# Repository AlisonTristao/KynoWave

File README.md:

# KynoWave

O **KynoWave** é um projeto de hardware focado na monitorização de ruído acústico em ambientes. Desenvolvido em torno do microcontrolador ESP32-S3. 

O projeto foi desenvolvido para participar do desafio da Maratona de Inovação 2026/1, realizada no evento Arena Ação Jr.

Todo o desenvolvimento de hardware e software foi realizado em menos de um mês, dentro do prazo proposto pelo desafio, e o projeto conquistou o 2º lugar na competição.

## Características Principais

* **Microcontrolador:** ESP32-S3.
* **Entradas de Áudio:** Capacidade para a ligação de até 2 microfones, com ganho ajustável entre 2x e 22x.
* **Filtro Anti-aliasing:** Filtro anti-aliasing configurado para 100kHz.
* **Ecrã LCD:** Conexão otimizada via cabo flat (FPC) para interface SPI com ecrã LCD.
* **Sensores Ambientais:** Integração com sensores de pressão, temperatura e humidade.
* **Armazenamento Local:** Interface para cartão de memória usando conexão SPI.
* **Expansibilidade:** Disponibilização de 15 GPIOs genéricos através de um conector lateral. Estes pinos permitem a adição de sensores extra e suportam integração com módulos de câmara e sensores i2c.

Abaixo, a fotografia detalhada da PCB:

---

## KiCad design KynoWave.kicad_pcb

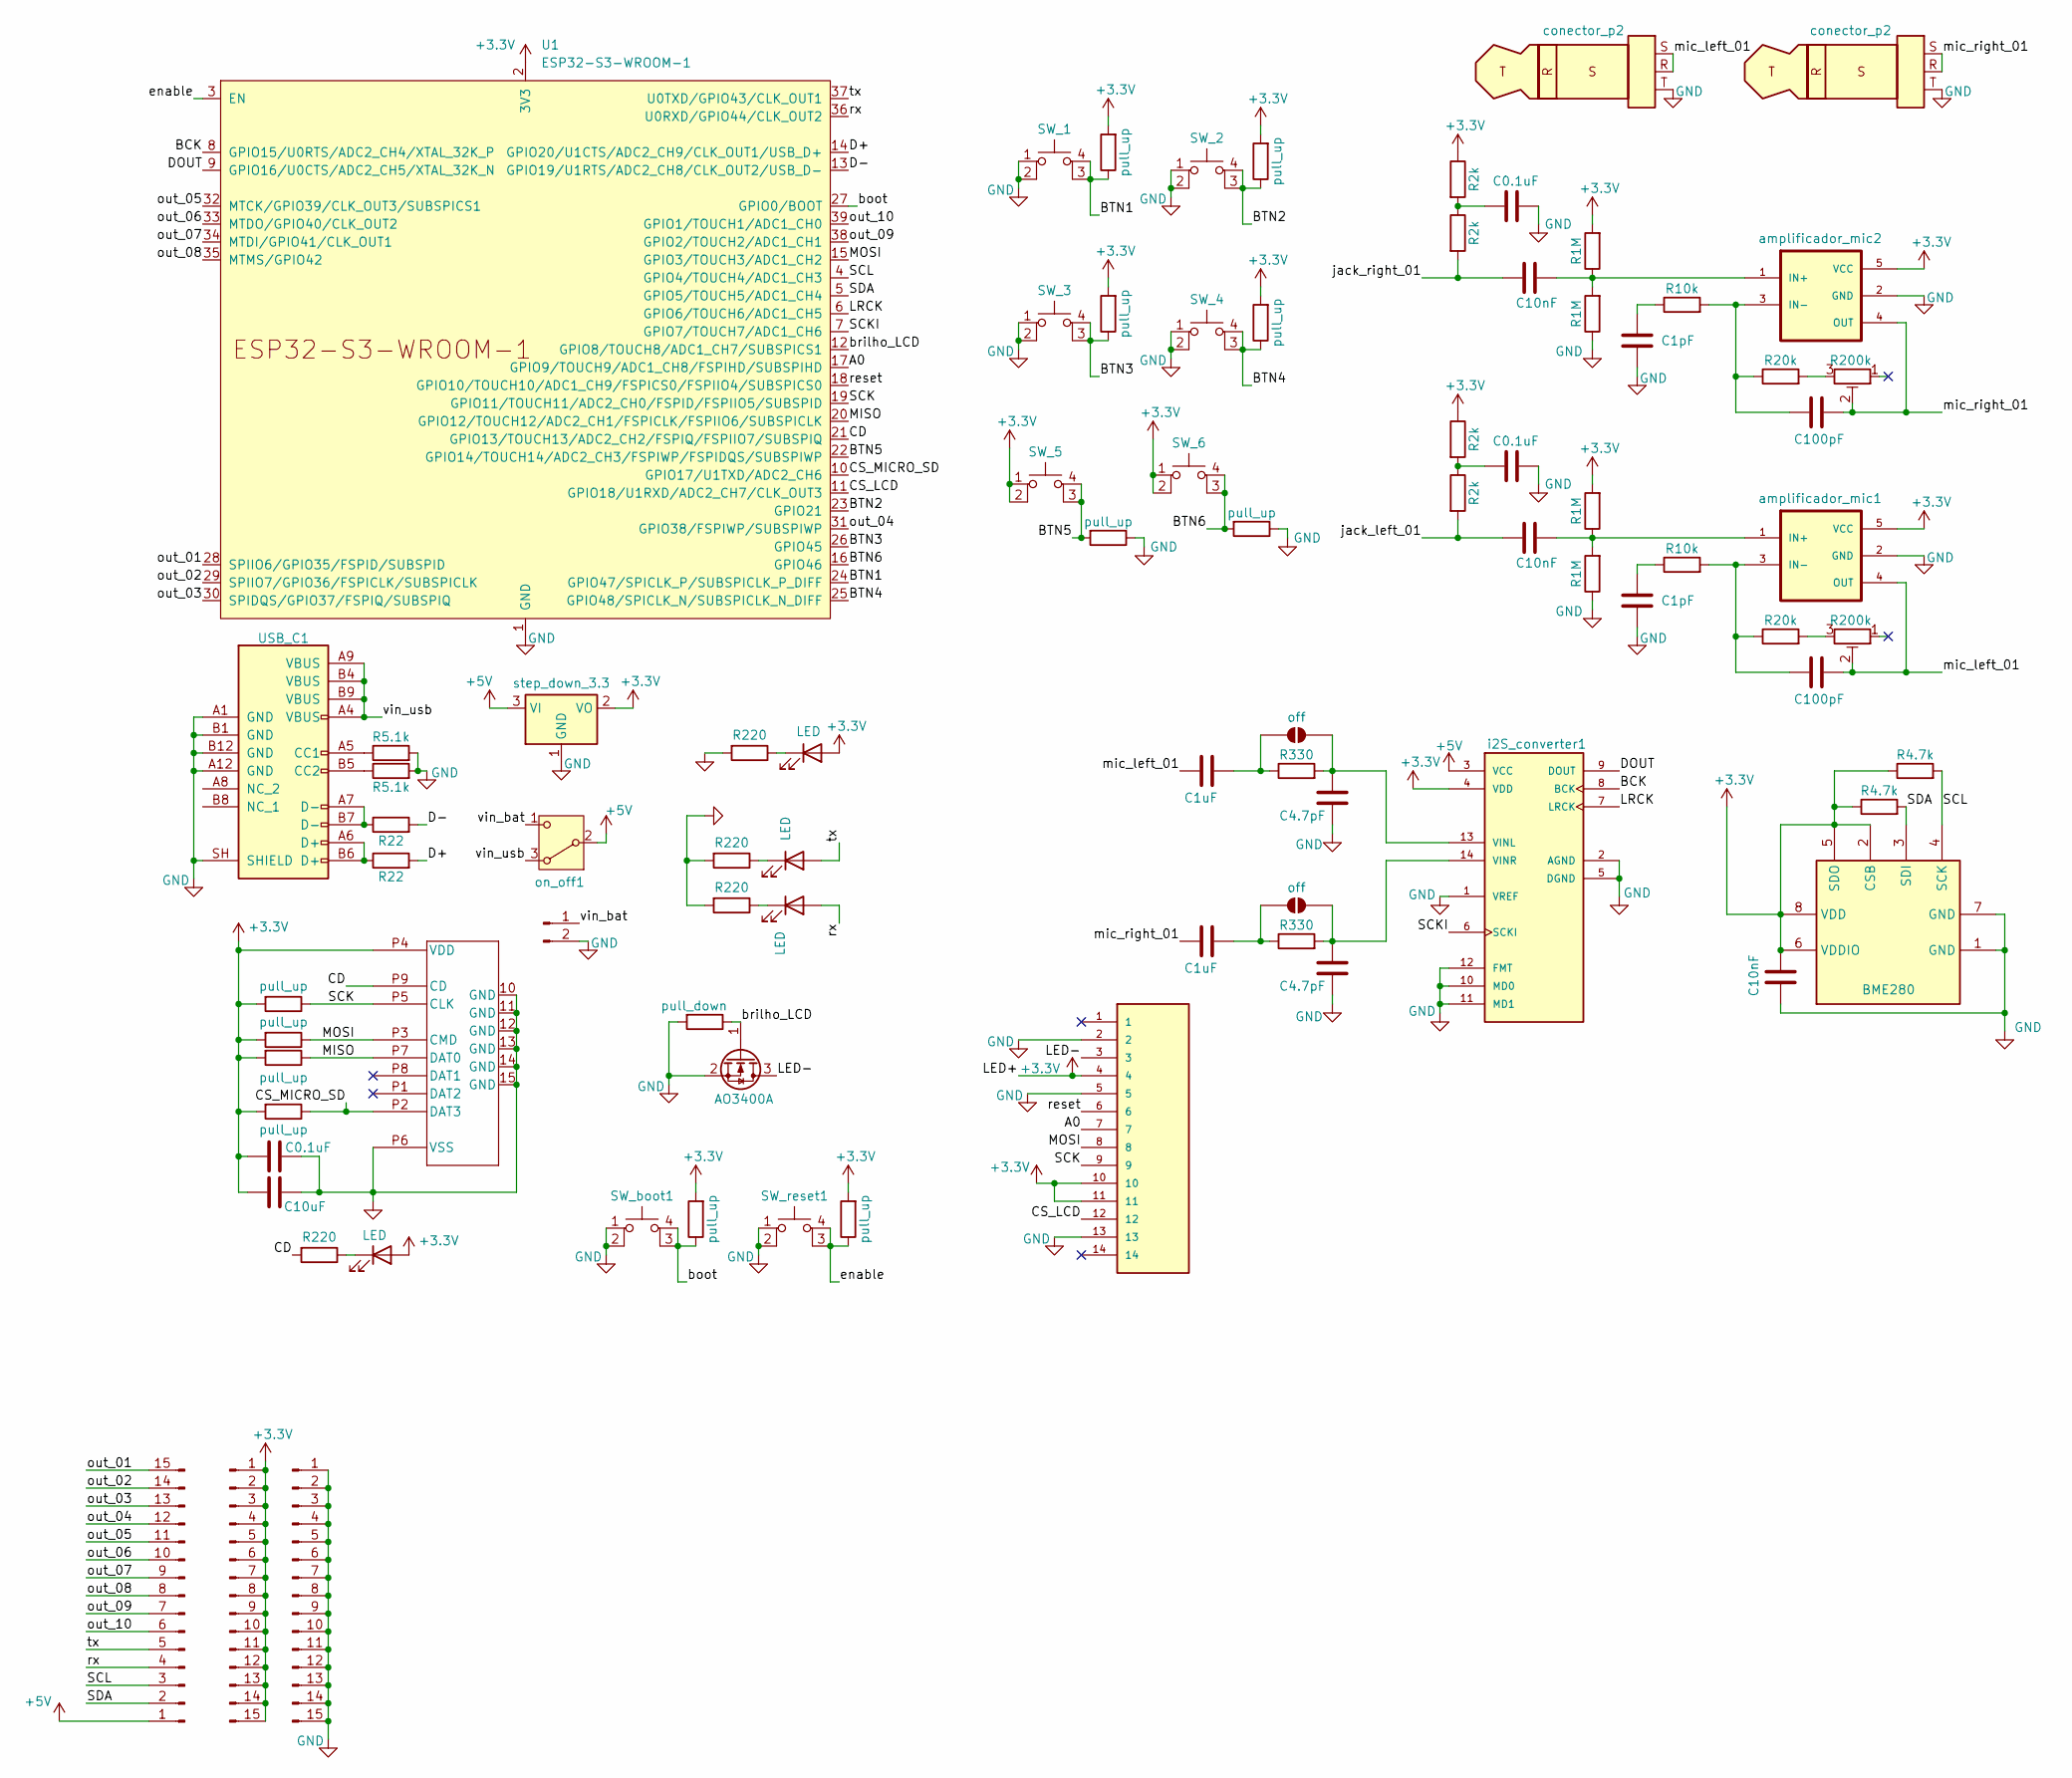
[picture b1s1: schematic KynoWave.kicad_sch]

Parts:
AudioPlug1, AudioPlug2: conector_p2; Jack_3.5mm_CUI_SJ-3523-SMT_Horizontal
C1, C8: C100pF; C_0805_2012Metric
C2, C7: C1pF; C_0805_2012Metric
C3, C6, C15: C10nF; C_0805_2012Metric
C4, C5, C9: C0.1uF; C_0805_2012Metric
C10: C10uF; C_0805_2012Metric
C11, C13: C1uF; C_0805_2012Metric
C12, C14: C4.7pF; C_0805_2012Metric
D4, D5, D6: LED; LED_0805_2012Metric
D7: LED; LED_D1.8mm_W1.8mm_H2.4mm_Horizontal_O1.27mm_Z1.6mm
J1: FFC2B35-14-G_REVA2; GCT_FFC2B35-14-G_REVA2; PARTREV A2
J2, J3, J4: Conn_01x15_Pin; PinHeader_1x15_P2.54mm_Vertical
J5: Conn_01x02_Pin; Molex_KK-254_AE-6410-02A_1x02_P2.54mm_Vertical
J6: MEM2075-00-140-01-A; MEM2075-00-140-01-A_GCT
JP1, JP2: off; SolderJumper-2_P1.3mm_Open_TrianglePad1.0x1.5mm
Q1: AO3400A; SOT-23
R1, R2: R5.1k; R_0805_2012Metric
R3, R4: R22; R_0805_2012Metric
R5, R6, R26, R27, R28, R29, R36, R37, R38, R39, R40, R41: pull_up; R_0805_2012Metric
R11, R25: R10k; R_0805_2012Metric
R12, R17, R24: R220; R_0805_2012Metric_Pad1.20x1.40mm_HandSolder
R13, R31: R20k; R_0805_2012Metric
R14, R15, R21, R22: R1M; R_0805_2012Metric
R16, R18, R19, R20: R2k; R_0805_2012Metric
R23: pull_down; R_0805_2012Metric
R30: R220; R_0805_2012Metric
R32, R33: R330; R_0805_2012Metric
R34, R35: R4.7k; R_0805_2012Metric
RV1, RV2: R200k; Potentiometer_Bourns_3314G_Vertical
SW_1, SW_2, SW_3, SW_4, SW_5, SW_6: SW_6mm_SMD; SW_TS08-66-43-BK-160-SMT-67-TR
SW_boot1: SW_6mm_SMD; SW_TS08-66-43-BK-160-SMT-67-TR
SW_reset1: SW_6mm_SMD; SW_TS08-66-43-BK-160-SMT-67-TR
U1: ESP32-S3-WROOM-1; ESP32-S3-WROOM-1U
U2: BME280; Bosch_LGA-8_2.5x2.5mm_P0.65mm_ClockwisePinNumbering
USB_C1: USB_C_Receptacle_USB2.0_14P; USB_C_Receptacle_XKB_U262-16XN-4BVC11
amplificador_mic1, amplificador_mic2: MAX4466EXK; SOT65P210X110-5N
i2S_converter1: PCM1808PWR; SOP65P640X120-14N; PARTREV B
on_off1: SW_Nidec_CAS-120A1; SW_SPDT_CK_JS102011SAQN
step_down_3.3: AMS1117-3.3; SOT-223-3_TabPin2

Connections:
+3.3V: C9.1, C10.1, C15.2, D6.2 (A), D7.2 (A), J1.4, J1.10, J1.11, J3.1, J3.2, J3.3, J3.4, J3.5, J3.6, J3.7, J3.8, J3.9, J3.10, J3.11, J3.12, J3.13, J3.14, J3.15, J6.P4 (VDD), R5.2, R6.2, R15.2, R18.1, R19.1, R21.2, R26.2, R27.2, R28.2, R29.2, R34.1, R35.1, R36.2, R37.2, R38.2, R39.2, SW_5.1, SW_5.2, SW_6.1, SW_6.2, U1.2 (3V3), U2.2 (CSB), U2.5 (SDO), U2.6 (VDDIO), U2.8 (VDD), amplificador_mic1.5 (VCC), amplificador_mic2.5 (VCC), i2S_converter1.4 (VDD), step_down_3.3.2 (VO)
+5V: J2.1, i2S_converter1.3 (VCC), on_off1.2 (B), step_down_3.3.3 (VI)
/A0: J1.7, U1.17 (GPIO9/TOUCH9/ADC1_CH8/FSPIHD/SUBSPIHD)
/BCK: U1.8 (GPIO15/U0RTS/ADC2_CH4/XTAL_32K_P), i2S_converter1.8 (BCK)
/BTN1: R36.1, SW_1.3 (K), SW_1.4 (A), U1.24 (GPIO47/SPICLK_P/SUBSPICLK_P_DIFF)
/BTN2: R37.1, SW_2.3 (K), SW_2.4 (A), U1.23 (GPIO21)
/BTN3: R38.1, SW_3.3 (K), SW_3.4 (A), U1.26 (GPIO45)
/BTN4: R39.1, SW_4.3 (K), SW_4.4 (A), U1.25 (GPIO48/SPICLK_N/SUBSPICLK_N_DIFF)
/BTN5: R40.2, SW_5.3 (K), SW_5.4 (A), U1.22 (GPIO14/TOUCH14/ADC2_CH3/FSPIWP/FSPIDQS/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)
/BTN6: R41.2, SW_6.3 (K), SW_6.4 (A), U1.16 (GPIO46)
/CD: J6.P9 (CD), R30.2, U1.21 (GPIO13/TOUCH13/ADC2_CH2/FSPIQ/FSPIIO7/S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)
/CS_LCD: J1.12, U1.11 (GPIO18/U1RXD/ADC2_CH7/CLK_OUT3)
/CS_MICRO_SD: J6.P2 (DAT3), R28.1, U1.10 (GPIO17/U1TXD/ADC2_CH6)
/D+: R3.2, U1.14 (GPIO20/U1CTS/ADC2_CH9/CLK_OUT1/USB_D+)
/D-: R4.2, U1.13 (GPIO19/U1RTS/ADC2_CH8/CLK_OUT2/USB_D-)
/DOUT: U1.9 (GPIO16/U0CTS/ADC2_CH5/XTAL_32K_N), i2S_converter1.9 (DOUT)
/LED-: J1.3, Q1.3 (D)
/LRCK: U1.6 (GPIO6/TOUCH6/ADC1_CH5), i2S_converter1.7 (LRCK)
/MISO: J6.P7 (DAT0), R26.1, U1.20 (GPIO12/TOUCH12/ADC2_CH1/FSPICLK/FSPIIO6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)
/MOSI: J1.8, J6.P3 (CMD), R27.1, U1.15 (GPIO3/TOUCH3/ADC1_CH2)
/SCK: J1.9, J6.P5 (CLK), R29.1, U1.19 (GPIO11/TOUCH11/ADC2_CH0/FSPID/FSPIIO5/S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)
/SCKI: U1.7 (GPIO7/TOUCH7/ADC1_CH6), i2S_converter1.6 (SCKI)
/SCL: J2.3, R35.2, U1.4 (GPIO4/TOUCH4/ADC1_CH3), U2.4 (SCK)
/SDA: J2.2, R34.2, U1.5 (GPIO5/TOUCH5/ADC1_CH4), U2.3 (SDI)
/boot: R5.1, SW_boot1.3 (K), SW_boot1.4 (A), U1.27 (GPIO0/BOOT)
/brilho_LCD: Q1.1 (G), R23.1, U1.12 (GPIO8/TOUCH8/ADC1_CH7/SUBSPICS1)
/enable: R6.1, SW_reset1.3 (K), SW_reset1.4 (A), U1.3 (EN)
/jack_left_01: C3.1, R16.2
/jack_right_01: C6.1, R20.2
/mic_left_01: AudioPlug1.R, AudioPlug1.S, C1.1, C13.2, RV1.2, amplificador_mic1.4 (OUT)
/mic_right_01: AudioPlug2.R, AudioPlug2.S, C8.1, C11.2, RV2.2, amplificador_mic2.4 (OUT)
/out_01: J2.15, U1.28 (SPIIO6/GPIO35/FSPID/SUBSPID)
/out_02: J2.14, U1.29 (SPIIO7/GPIO36/FSPICLK/SUBSPICLK)
/out_03: J2.13, U1.30 (SPIDQS/GPIO37/FSPIQ/SUBSPIQ)
/out_04: J2.12, U1.31 (GPIO38/FSPIWP/SUBSPIWP)
/out_05: J2.11, U1.32 (MTCK/GPIO39/CLK_OUT3/SUBSPICS1)
/out_06: J2.10, U1.33 (MTDO/GPIO40/CLK_OUT2)
/out_07: J2.9, U1.34 (MTDI/GPIO41/CLK_OUT1)
/out_08: J2.8, U1.35 (MTMS/GPIO42)
/out_09: J2.7, U1.38 (GPIO2/TOUCH2/ADC1_CH1)
/out_10: J2.6, U1.39 (GPIO1/TOUCH1/ADC1_CH0)
/reset: J1.6, U1.18 (GPIO10/TOUCH10/ADC1_CH9/FSPICS0/FSPIIO4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)
/rx: D5.2 (A), J2.4, U1.36 (U0RXD/GPIO44/CLK_OUT2)
/tx: D4.2 (A), J2.5, U1.37 (U0TXD/GPIO43/CLK_OUT1)
/vin_bat: J5.1, on_off1.1 (C)
/vin_usb: USB_C1.A4 (VBUS), USB_C1.A9 (VBUS), USB_C1.B4 (VBUS), USB_C1.B9 (VBUS), on_off1.3 (A)
GND: AudioPlug1.T, AudioPlug2.T, C2.2, C4.1, C5.1, C7.2, C9.2, C10.2, C12.2, C14.2, C15.1, J1.2, J1.5, J1.13, J4.1, J4.2, J4.3, J4.4, J4.5, J4.6, J4.7, J4.8, J4.9, J4.10, J4.11, J4.12, J4.13, J4.14, J4.15, J5.2, J6.10 (GND), J6.11 (GND), J6.12 (GND), J6.13 (GND), J6.14 (GND), J6.15 (GND), J6.P6 (VSS), Q1.2 (S), R1.2, R2.2, R12.2, R14.1, R17.2, R22.1, R23.2, R24.2, R40.1, R41.1, SW_1.1, SW_1.2, SW_2.1, SW_2.2, SW_3.1, SW_3.2, SW_4.1, SW_4.2, SW_boot1.1, SW_boot1.2, SW_reset1.1, SW_reset1.2, U1.1 (GND), U1.40 (GND), U1.41 (GND), U2.1 (GND), U2.7 (GND), USB_C1.A1 (GND), USB_C1.A12 (GND), USB_C1.B1 (GND), USB_C1.B12 (GND), USB_C1.SH (SHIELD), amplificador_mic1.2 (GND), amplificador_mic2.2 (GND), i2S_converter1.1 (VREF), i2S_converter1.2 (AGND), i2S_converter1.5 (DGND), i2S_converter1.10 (MD0), i2S_converter1.11 (MD1), i2S_converter1.12 (FMT), step_down_3.3.1 (GND)
unnamed: C2.1, R11.1
unnamed: C4.2, R16.1, R18.2
unnamed: C5.2, R19.2, R20.1
unnamed: C7.1, R25.1
unnamed: D4.1 (K), R12.1
unnamed: D5.1 (K), R17.1
unnamed: D6.1 (K), R30.1
unnamed: D7.1 (K), R24.1
unnamed: C13.1, JP1.1 (A), R33.1
unnamed: C14.1, JP1.2 (B), R33.2, i2S_converter1.13 (VINL)
unnamed: C11.1, JP2.1 (A), R32.1
unnamed: C12.1, JP2.2 (B), R32.2, i2S_converter1.14 (VINR)
unnamed: R3.1, USB_C1.A6 (D+), USB_C1.B6 (D+)
unnamed: R4.1, USB_C1.A7 (D-), USB_C1.B7 (D-)
unnamed: R13.2, RV1.3
unnamed: R31.2, RV2.3
unnamed: R1.1, USB_C1.A5 (CC1)
unnamed: R2.1, USB_C1.B5 (CC2)
unnamed: C3.2, R14.2, R15.1, amplificador_mic1.1 (IN+)
unnamed: C1.2, R11.2, R13.1, amplificador_mic1.3 (IN-)
unnamed: C6.2, R21.1, R22.2, amplificador_mic2.1 (IN+)
unnamed: C8.2, R25.2, R31.1, amplificador_mic2.3 (IN-)

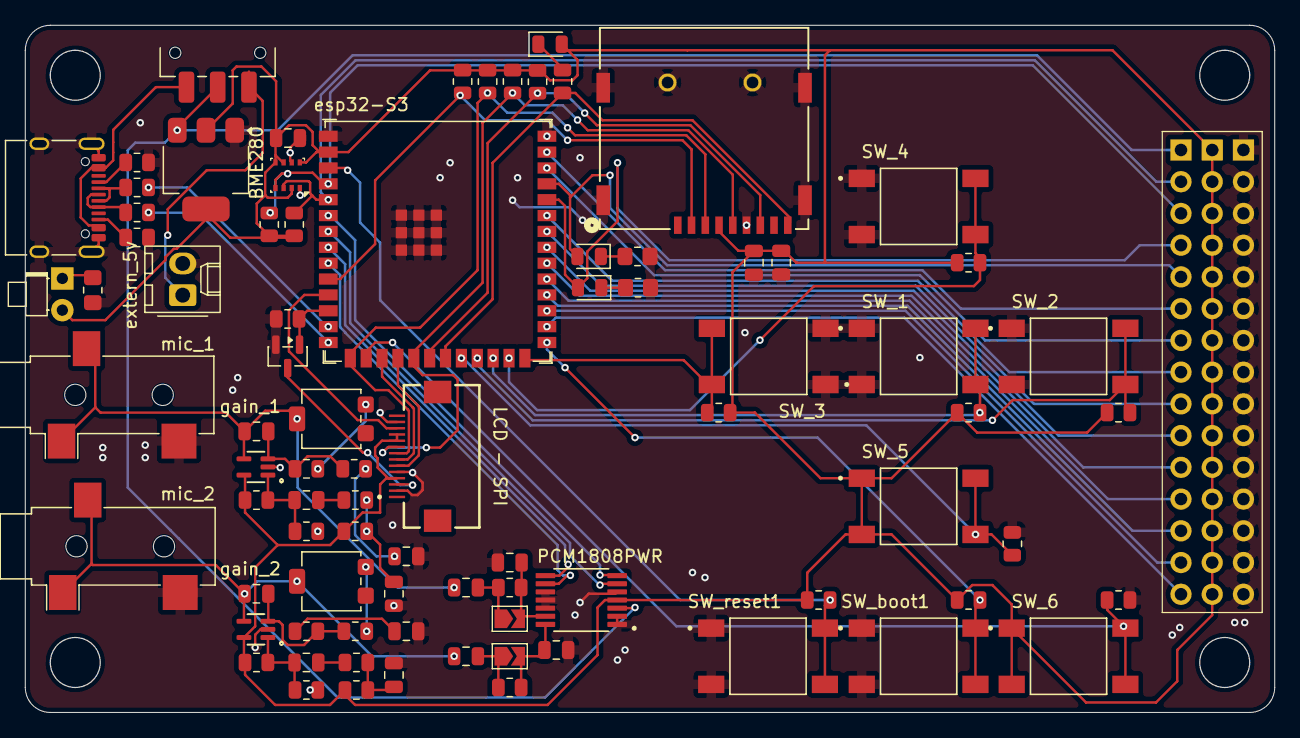
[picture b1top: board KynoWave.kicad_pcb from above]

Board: 2 copper layers, 100.0 x 55.0 mm, 85 parts (0 on the bottom side), 69 nets.

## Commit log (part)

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2026-05-03 salvando a codicao inicial antes do roteamento
2026-05-03 antes das trilhas
2026-05-03 fiz as trilhas
2026-05-06 praticamente pronto
2026-05-06 Create README.md for KynoWave
    Added project overview and key features for KynoWave.
2026-05-14 Atualizando referência da pasta de hardware
2026-05-14 apaguei o history fodase
2026-05-14 primeiro commmit
2026-05-15 logger parece funcionar
2026-05-15 lixo
2026-05-15 antes de mudar o logger pra um buffer
2026-05-15 conteudo generico no content do logger
2026-05-15 formatacao de printf
2026-05-15 comecei a organizar
2026-05-15 adiconei o shell
2026-05-16 terminal funfa tudo funfa
2026-05-16 mudei o shared type para ser compativel com espnow
2026-05-16 fiuncao esquecida
2026-05-16 organiazando...
2026-05-16 organizando a task
2026-05-17 temos display
2026-05-17 temos OTA
2026-05-17 temos MQTT
2026-05-17 alteracoes
2026-05-18 organizacao e hub de entradas e saida
2026-05-18 comentarios e padronizacao das tags de wigi
2026-05-18 correcao bugs
2026-05-18 temos interface visual
2026-05-18 comentarios
2026-05-19 tirei a poha da lib da adafruit
2026-05-19 barra superior funcionando
2026-05-19 arrumei o terminal
2026-05-19 saida duplicada do terminal
2026-05-19 reconect no mqtt certo
2026-05-21 temos leds
2026-05-21 alteracoes boladas
2026-05-21 funcionouuu
2026-05-21 tirei o tipo pacote pq ia dar ruim com i2s e mqtt
2026-05-21 arrumando o ping do mqtt
2026-05-21 ordem do pinos e pwm no led verde
2026-05-22 dale funcionou
2026-05-22 final
2026-05-22 codigo python
2026-05-22 funciona com transmissao de audio
2026-05-25 tirando lixo
2026-05-25 atualizando a colocao no readme
